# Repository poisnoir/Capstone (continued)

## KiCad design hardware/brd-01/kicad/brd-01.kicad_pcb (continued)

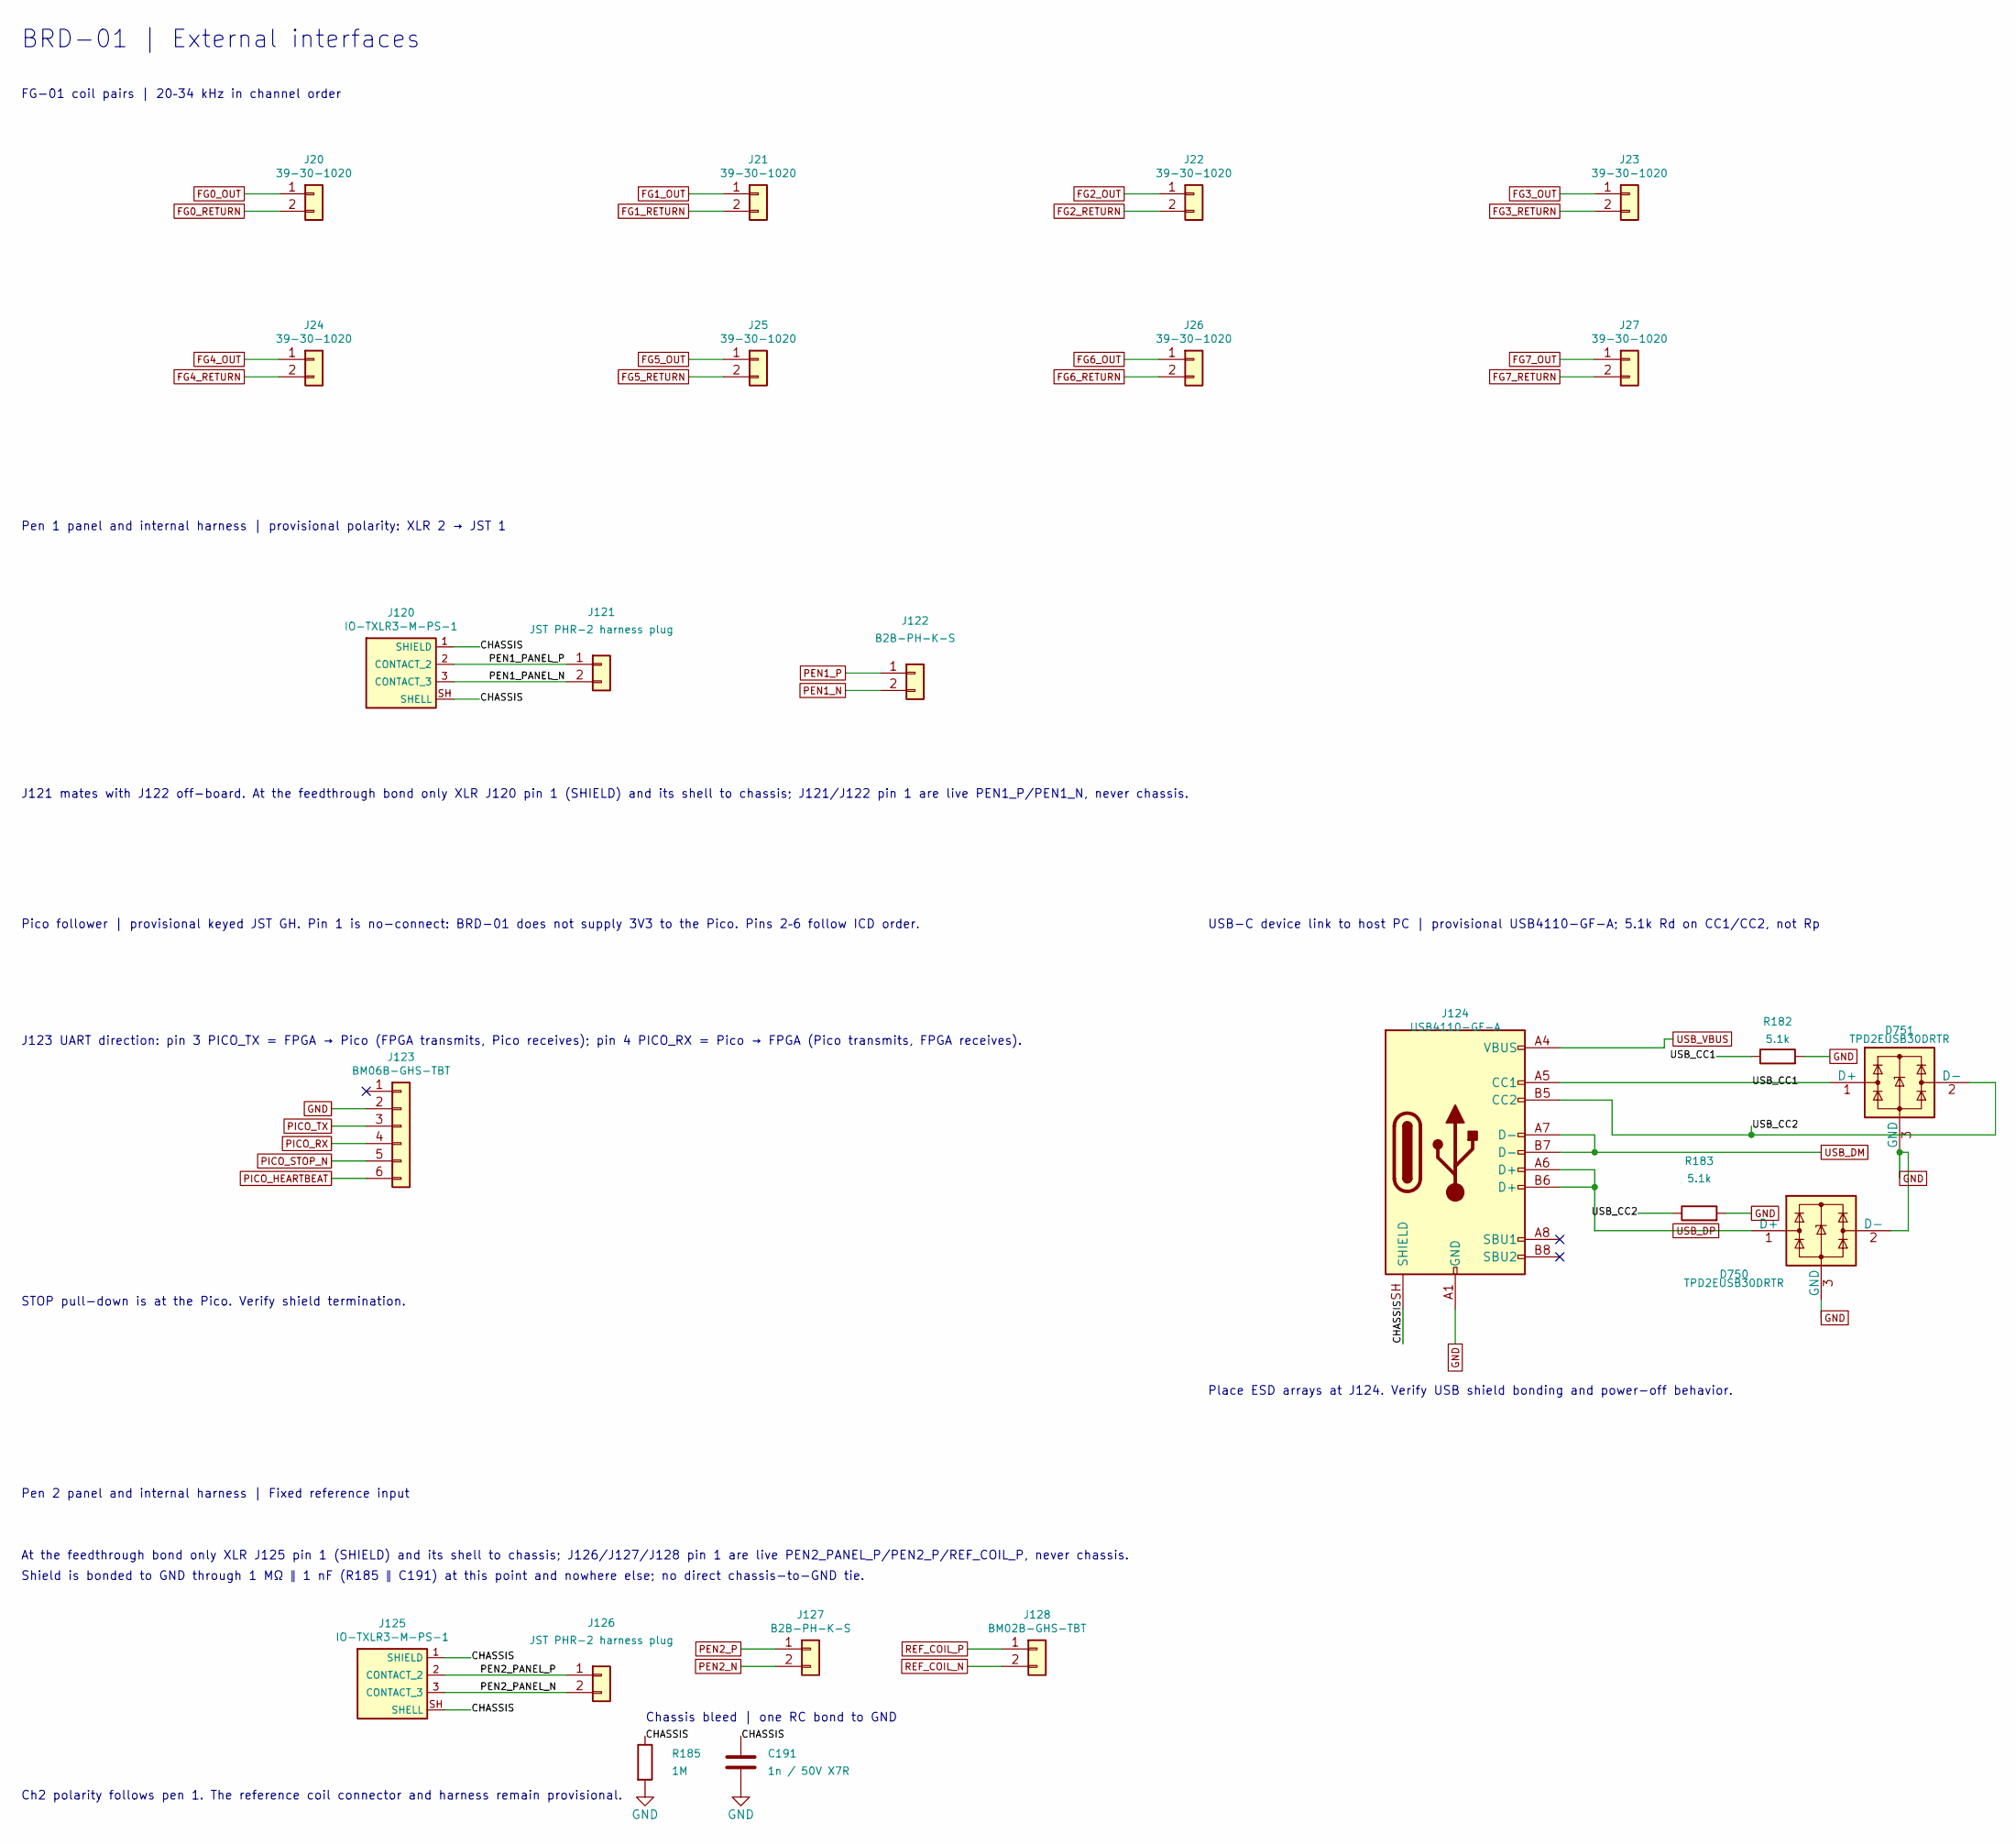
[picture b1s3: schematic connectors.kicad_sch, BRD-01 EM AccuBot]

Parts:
C191: 1n / 50V X7R; C_0603_1608Metric
D750, D751: TPD2EUSB30DRTR; Texas_DRT-3
J20, J21, J22, J23, J24, J25, J26, J27: 39-30-1020; Molex_Mini-Fit_Jr_5569-02A2_2x01_P4.20mm_Horizontal
J120, J125: IO-TXLR3-M-PS-1
J121, J126: JST PHR-2 harness plug
J122, J127: B2B-PH-K-S; JST_PH_B2B-PH-K_1x02_P2.00mm_Vertical
J123: BM06B-GHS-TBT; JST_GH_BM06B-GHS-TBT_1x06-1MP_P1.25mm_Vertical
J124: USB4110-GF-A; USB_C_Receptacle_GCT_USB4110
J128: BM02B-GHS-TBT; JST_GH_BM02B-GHS-TBT_1x02-1MP_P1.25mm_Vertical
R182, R183: 5.1k; R_0603_1608Metric
R185: 1M; R_0603_1608Metric

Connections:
/connectors/CHASSIS: C191.1, J120.1 (SHIELD), J120.SH (SHELL), J124.SH (SHIELD), J125.1 (SHIELD), J125.SH (SHELL), R185.1
/connectors/USB_CC1: D751.1 (D+), J124.A5 (CC1), R182.1
/connectors/USB_CC2: D751.2 (D-), J124.B5 (CC2), R183.1
FG0_OUT: J20.1; also elsewhere on the board
FG0_RETURN: J20.2; also elsewhere on the board
FG1_OUT: J21.1; also elsewhere on the board
FG1_RETURN: J21.2; also elsewhere on the board
FG2_OUT: J22.1; also elsewhere on the board
FG2_RETURN: J22.2; also elsewhere on the board
FG3_OUT: J23.1; also elsewhere on the board
FG3_RETURN: J23.2; also elsewhere on the board
FG4_OUT: J24.1; also elsewhere on the board
FG4_RETURN: J24.2; also elsewhere on the board
FG5_OUT: J25.1; also elsewhere on the board
FG5_RETURN: J25.2; also elsewhere on the board
FG6_OUT: J26.1; also elsewhere on the board
FG6_RETURN: J26.2; also elsewhere on the board
FG7_OUT: J27.1; also elsewhere on the board
FG7_RETURN: J27.2; also elsewhere on the board
GND: C191.2, D750.2 (D-), D750.3 (GND), D751.3 (GND), J123.2, J124.A1 (GND), J124.A12 (GND), J124.B1 (GND), J124.B12 (GND), R182.2, R183.2, R185.2; also elsewhere on the board
unnamed: J120.2 (CONTACT_2), J121.1
unnamed: J120.3 (CONTACT_3), J121.2
unnamed: J125.2 (CONTACT_2), J126.1
unnamed: J125.3 (CONTACT_3), J126.2
PEN1_N: J122.2; also elsewhere on the board
PEN1_P: J122.1; also elsewhere on the board
PEN2_N: J127.2; also elsewhere on the board
PEN2_P: J127.1; also elsewhere on the board
PICO_HEARTBEAT: J123.6; also elsewhere on the board
PICO_RX: J123.4; also elsewhere on the board
PICO_STOP_N: J123.5; also elsewhere on the board
PICO_TX: J123.3; also elsewhere on the board
REF_COIL_N: J128.2; also elsewhere on the board
REF_COIL_P: J128.1; also elsewhere on the board
USB_DM: J124.A7 (D-), J124.B7 (D-); also elsewhere on the board
USB_DP: D750.1 (D+), J124.A6 (D+), J124.B6 (D+); also elsewhere on the board
USB_VBUS: J124.A4 (VBUS), J124.A9 (VBUS), J124.B4 (VBUS), J124.B9 (VBUS); also elsewhere on the board

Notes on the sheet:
J123 UART direction: pin 3 PICO_TX = FPGA → Pico (FPGA transmits, Pico receives); pin 4 PICO_RX = Pico → FPGA (Pico transmits, FPGA receives).
Pico follower | provisional keyed JST GH. Pin 1 is no-connect: BRD-01 does not supply 3V3 to the Pico. Pins 2–6 follow ICD order.
J121 mates with J122 off-board. At the feedthrough bond only XLR J120 pin 1 (SHIELD) and its shell to chassis; J121/J122 pin 1 are live PEN1_P/PEN1_N, never chassis.
FG-01 coil pairs | 20–34 kHz in channel order
Shield is bonded to GND through 1 MΩ ∥ 1 nF (R185 ∥ C191) at this point and nowhere else; no direct chassis-to-GND tie.
USB-C device link to host PC | provisional USB4110-GF-A; 5.1k Rd on CC1/CC2, not Rp
Pen 2 panel and internal harness | Fixed reference input
Pen 1 panel and internal harness | provisional polarity: XLR 2 → JST 1
At the feedthrough bond only XLR J125 pin 1 (SHIELD) and its shell to chassis; J126/J127/J128 pin 1 are live PEN2_PANEL_P/PEN2_P/REF_COIL_P, never chassis.
BRD-01 | External interfaces
Chassis bleed | one RC bond to GND
Ch2 polarity follows pen 1. The reference coil connector and harness remain provisional.
STOP pull-down is at the Pico. Verify shield termination.
Place ESD arrays at J124. Verify USB shield bonding and power-off behavior.

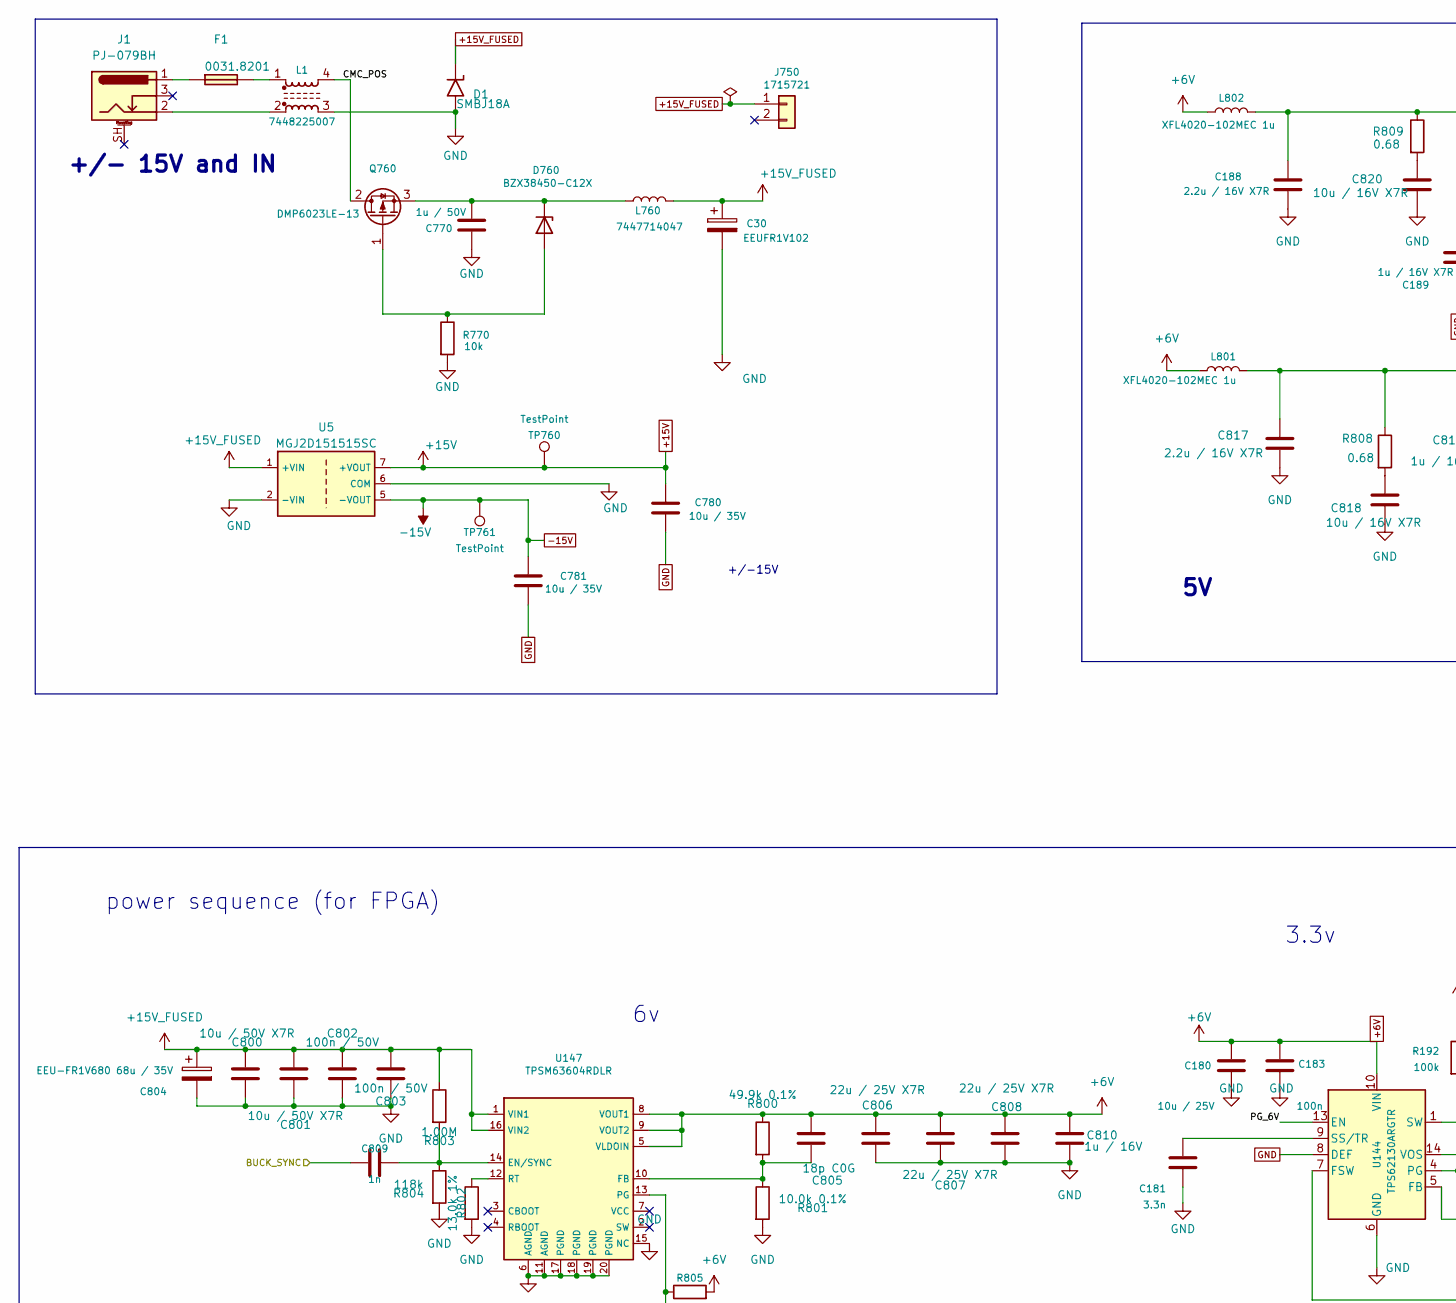
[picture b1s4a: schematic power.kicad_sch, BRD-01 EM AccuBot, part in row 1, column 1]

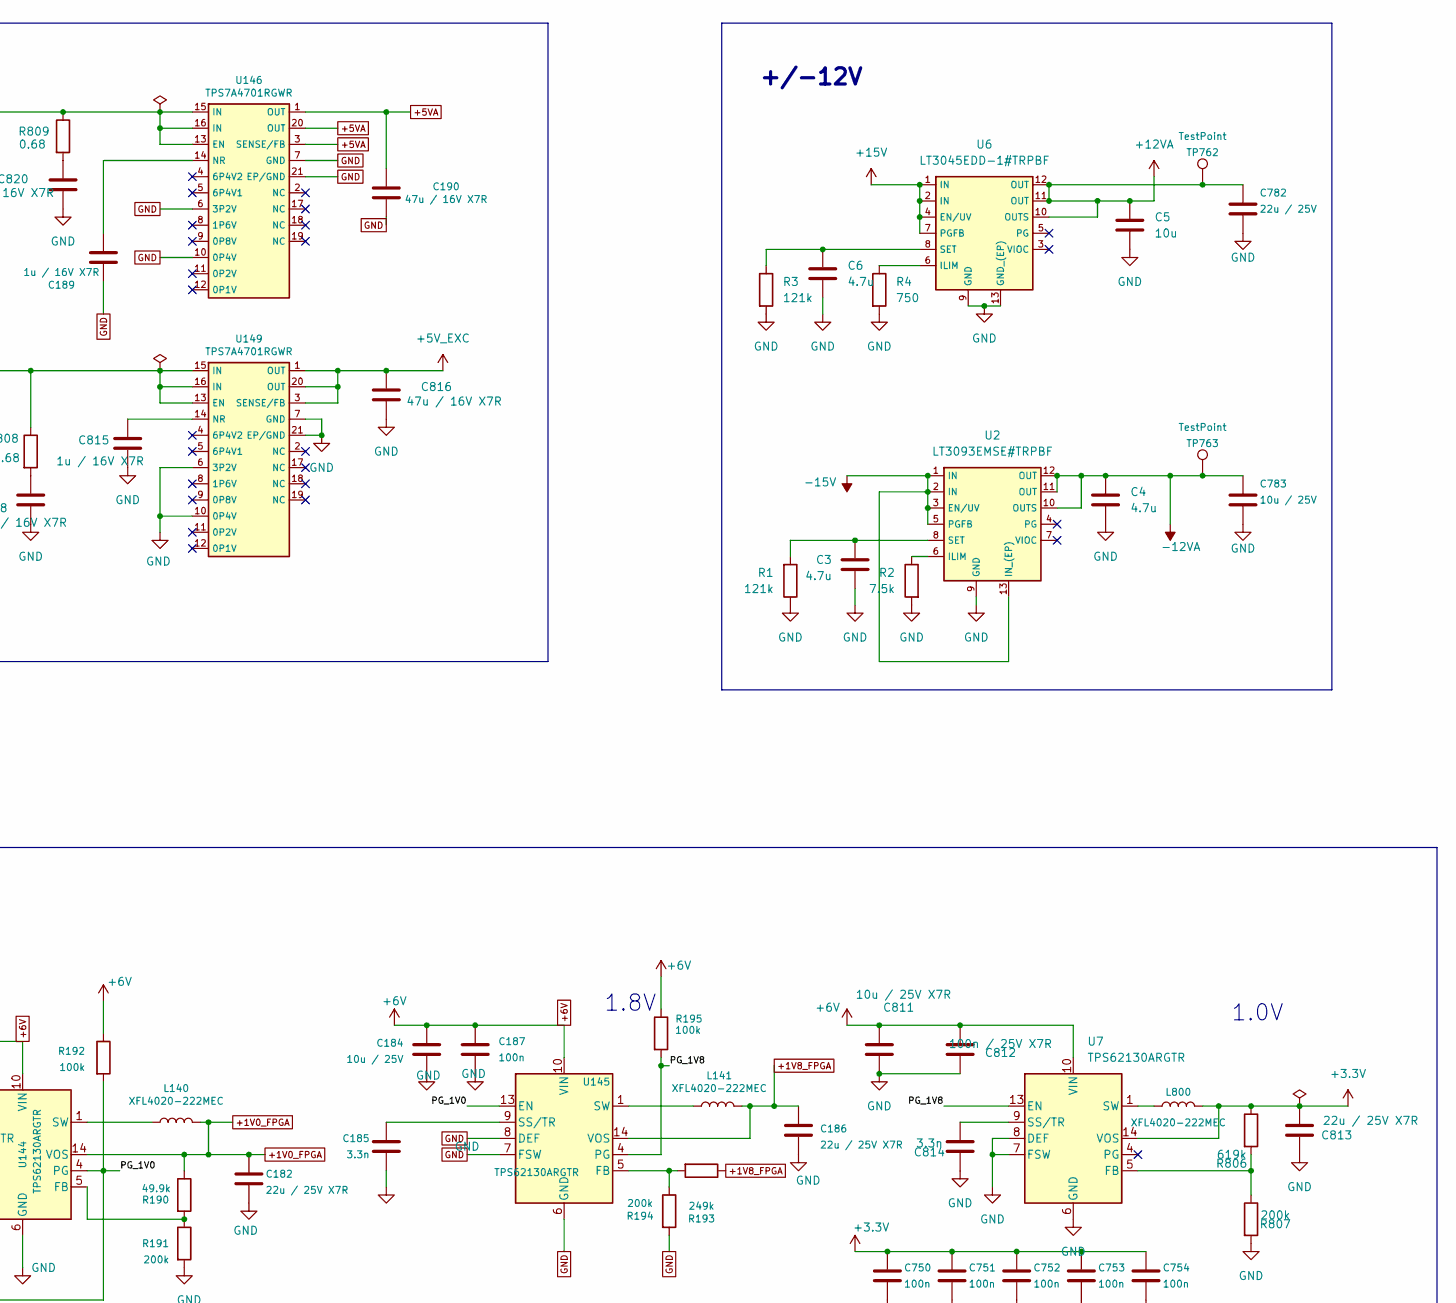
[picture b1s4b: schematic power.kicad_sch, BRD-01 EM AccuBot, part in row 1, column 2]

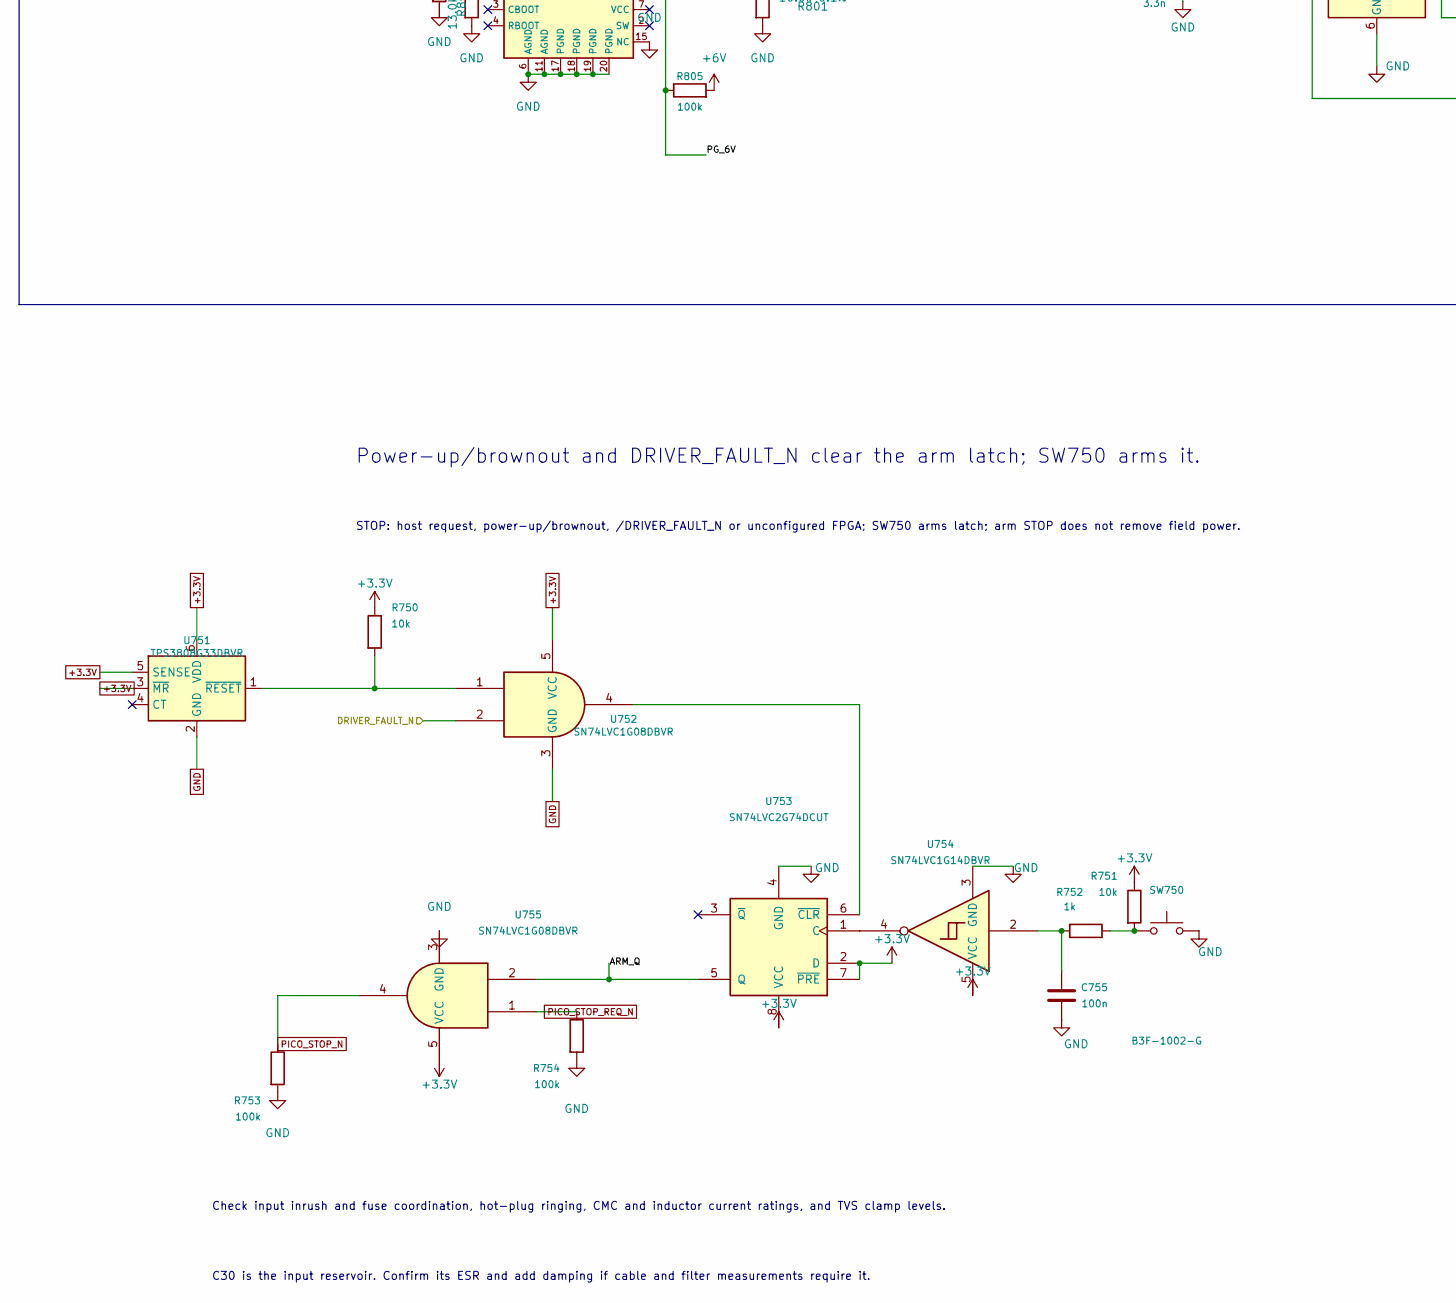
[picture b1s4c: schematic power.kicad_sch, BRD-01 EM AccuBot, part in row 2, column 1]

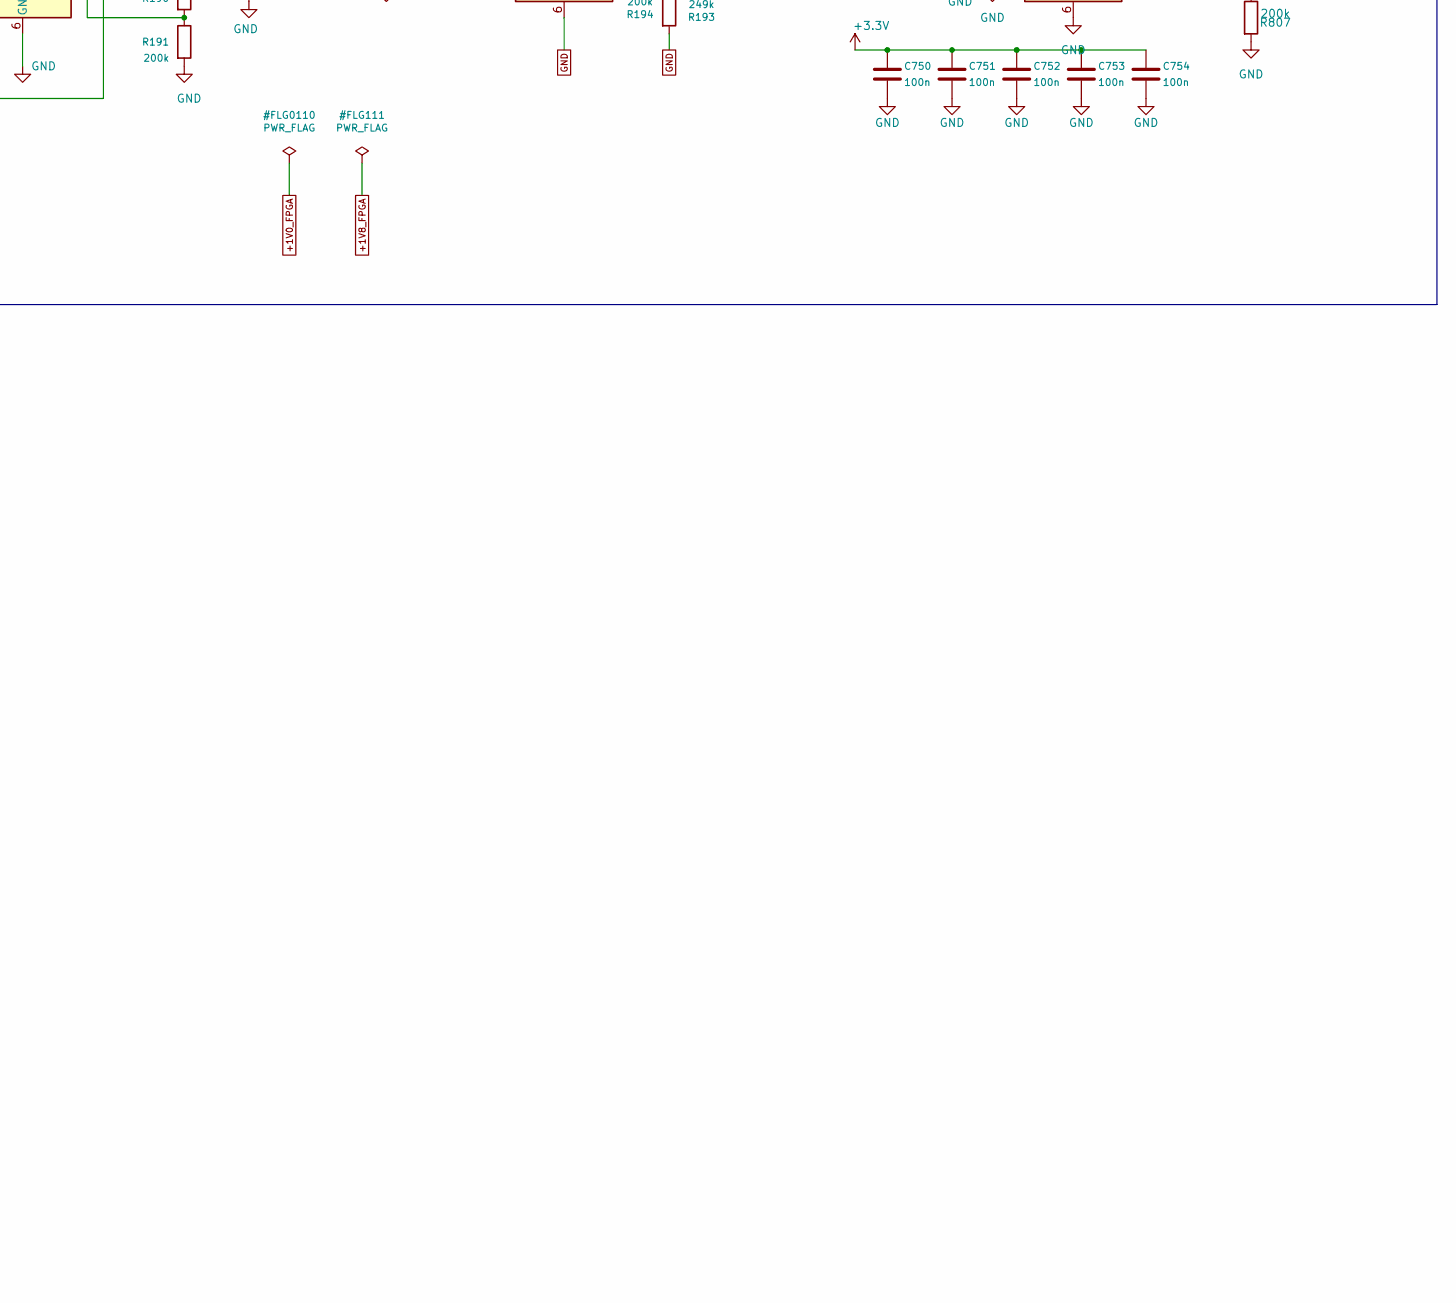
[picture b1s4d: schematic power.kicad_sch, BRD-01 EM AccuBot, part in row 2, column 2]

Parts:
C3, C6: 4.7u; C_0805_2012Metric
C4: 4.7u; C_1206_3216Metric
C5: 10u; C_1206_3216Metric
C30: EEUFR1V102; CP_Radial_D12.5mm_P5.00mm
C180, C184: 10u / 25V; C_1206_3216Metric
C181, C185, C814: 3.3n; C_0603_1608Metric
C182, C186, C806, C807, C808, C813: 22u / 25V X7R; C_1210_3225Metric
C183, C187, C750, C751, C752, C753, C754, C755: 100n; C_0603_1608Metric
C188, C817: 2.2u / 16V X7R; C_0805_2012Metric
C189: 1u / 16V X7R; C_1206_3216Metric
C190, C816: 47u / 16V X7R; C_1210_3225Metric
C770: 1u / 50V; C_1206_3216Metric
C780, C781: 10u / 35V; C_1206_3216Metric
C782: 22u / 25V; C_1210_3225Metric
C783: 10u / 25V; C_1210_3225Metric
C800, C801: 10u / 50V X7R; C_1210_3225Metric
C802, C803: 100n / 50V; C_0603_1608Metric
C804: EEU-FR1V680 68u / 35V; CP_Radial_D6.3mm_P2.50mm
C805: 18p C0G; C_0603_1608Metric
C809: 1n; C_0603_1608Metric
C810: 1u / 16V; C_0603_1608Metric
C811: 10u / 25V X7R; C_1206_3216Metric
C812: 100n / 25V X7R; C_0603_1608Metric
C815: 1u / 16V X7R; C_0603_1608Metric
C818, C820: 10u / 16V X7R; C_0805_2012Metric
D1: SMBJ18A; ST_SMBJ_DO-214AA_DS1283
D760: BZX38450-C12X; D_SOD-323
F1: 0031.8201; Fuseholder_Cylinder-5x20mm_Schurter_0031_8201_Horizontal_Op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; MPN 0001.2509
J1: PJ-079BH; BarrelJack_CUI_PJ-079BH_Horizontal
J750: 1715721; TerminalBlock_Phoenix_MKDS-1,5-2-5.08_1x02_P5.08mm_Horizont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
L1: 7448225007; Wuerth_WE-CMB-HC_S_7448225007
L140, L141, L800: XFL4020-222MEC; L_Coilcraft_XxL4020
L760: 7447714047; Wuerth_WE-PD_1050_7447714047
L801, L802: XFL4020-102MEC 1u; L_Coilcraft_XxL4020
Q760: DMP6023LE-13; SOT-223-3_TabPin2
R1, R3: 121k; R_0603_1608Metric
R2: 7.5k; R_0603_1608Metric
R4: 750; R_0603_1608Metric
R190: 49.9k; R_0603_1608Metric
R191, R194, R807: 200k; R_0603_1608Metric
R192, R195, R753, R754, R805: 100k; R_0603_1608Metric
R193: 249k; R_0603_1608Metric
R750, R751, R770: 10k; R_0603_1608Metric
R752: 1k; R_0603_1608Metric
R800: 49.9k 0.1%; R_0603_1608Metric
R801: 10.0k 0.1%; R_0603_1608Metric
R802: 13.0k 1%; R_0603_1608Metric
R803: 1.00M; R_0603_1608Metric
R804: 118k; R_0603_1608Metric
R806: 619k; R_0603_1608Metric
R808, R809: 0.68; R_0603_1608Metric
SW750: B3F-1002-G; SW_PUSH_6mm_H4.3mm
TP760, TP761, TP762, TP763: TestPoint; TestPoint_Pad_D1.5mm
U2: LT3093EMSE#TRPBF; MSOP-12-1EP_3x4.039mm_P0.65mm_EP1.651x2.845mm
U5: MGJ2D151515SC; Converter_DCDC_Murata_MGJ2DxxxxxxSC_THT
U6: LT3045EDD-1#TRPBF; DFN-12-1EP_3x3mm_P0.45mm_EP1.65x2.38mm
U7, U144, U145: TPS62130ARGTR; VQFN-16-1EP_3x3mm_P0.5mm_EP1.68x1.68mm_ThermalVias
U146, U149: TPS7A4701RGWR; Texas_RGW0020A_VQFN-20-1EP_5x5mm_P0.65mm_EP3.15x3.15mm_Ther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
U147: TPSM63604RDLR; TI_RDL0020A_B3QFN-20_5x5.5mm
U751: TPS3808G33DBVR; SOT-23-6
U752, U755: SN74LVC1G08DBVR; SOT-23-5
U753: SN74LVC2G74DCUT; VSSOP-8_2.3x2mm_P0.5mm
U754: SN74LVC1G14DBVR; SOT-23-5

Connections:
+1V0_FPGA: C182.1, L140.2, R190.1, U144.14 (VOS); also elsewhere on the board
+1V8_FPGA: C186.1, L141.2, R193.1, U145.14 (VOS); also elsewhere on the board
+3.3V: C750.1, C751.1, C752.1, C753.1, C754.1, C813.1, L800.2, R750.1, R751.1, R806.1, U7.14 (VOS), U751.3 (~MR), U751.5 (SENSE), U751.6 (VDD), U752.5 (VCC), U753.2 (D), U753.7 (~PRE), U753.8 (VCC), U754.5 (VCC), U755.5 (VCC); also elsewhere on the board
+5VA: C190.1, U146.1 (OUT), U146.3 (SENSE/FB), U146.20 (OUT); also elsewhere on the board
+5V_EXC: C816.1, U149.1 (OUT), U149.3 (SENSE/FB), U149.20 (OUT); also elsewhere on the board
+6V: C180.1, C183.1, C184.1, C187.1, C805.1, C806.1, C807.1, C808.1, C810.1, C811.1, C812.1, L801.1, L802.1, R192.1, R195.1, R800.1, R805.2, U7.10 (VIN), U7.11 (VIN), U7.12 (VIN), U144.10 (VIN), U144.11 (VIN), U144.12 (VIN), U145.10 (VIN), U145.11 (VIN), U145.12 (VIN), U147.5 (VLDOIN), U147.8 (VOUT1), U147.9 (VOUT2)
+12VA: C5.1, C782.1, TP762.1 (1_1), U6.10 (OUTS), U6.11 (OUT), U6.12 (OUT); also elsewhere on the board
+15V: C780.1, TP760.1 (1_1), U5.7 (+VOUT), U6.1 (IN), U6.2 (IN), U6.4 (EN/UV), U6.7 (PGFB)
+15V_FUSED: C30.1, C800.1, C801.1, C802.1, C803.1, C804.1, D1.1 (K), J750.1 (Pin_1_1), L760.2, R803.1, U5.1 (+VIN), U147.1 (VIN1), U147.16 (VIN2); also elsewhere on the board
-12VA: C4.1, C783.1, TP763.1 (1_1), U2.10 (OUTS), U2.11 (OUT), U2.12 (OUT); also elsewhere on the board
-15V: C781.1, TP761.1 (1_1), U2.1 (IN), U2.2 (IN), U2.3 (EN/UV), U2.5 (PGFB), U2.13 (IN_(EP)), U5.5 (-VOUT)
/BUCK_SYNC: C809.1; also elsewhere on the board
/DRIVER_FAULT_N: U752.2; also elsewhere on the board
/power/ARM_Q: U753.5 (Q), U755.2
/power/CMC_POS: L1.4, Q760.2 (D)
/power/PG_1V0: R192.2, U144.4 (PG), U144.7 (FSW), U145.13 (EN)
/power/PG_1V8: R195.2, U7.13 (EN), U145.4 (PG)
/power/PG_6V: R805.1, U144.13 (EN), U147.13 (PG)
GND: C3.2, C4.2, C5.2, C6.2, C30.2, C180.2, C181.2, C182.2, C183.2, C184.2, C185.2, C186.2, C187.2, C188.2, C189.2, C190.2, C750.2, C751.2, C752.2, C753.2, C754.2, C755.2, C770.2, C780.2, C781.2, C782.2, C783.2, C800.2, C801.2, C802.2, C803.2, C804.2, C806.2, C807.2, C808.2, C810.2, C811.2, C812.2, C813.2, C814.2, C815.2, C816.2, C817.2, C818.2, C820.2, D1.2 (A), L1.3, R1.1, R2.2, R3.2, R4.2, R191.2, R194.2, R753.2, R754.2, R770.2, R801.2, R802.2, R804.2, R807.2, SW750.2, U2.9 (GND), U5.2 (-VIN), U5.6 (COM), U6.9 (GND), U6.13 (GND_(EP)), U7.6 (GND), U7.7 (FSW), U7.8 (DEF), U7.15 (GND), U7.16 (GND), U7.17 (GND), U144.6 (GND), U144.8 (DEF), U144.15 (GND), U144.16 (GND), U144.17 (GND), U145.6 (GND), U145.7 (FSW), U145.8 (DEF), U145.15 (GND), U145.16 (GND), U145.17 (GND), U146.6 (3P2V), U146.7 (GND), U146.10 (0P4V), U146.21 (EP/GND), U147.6 (AGND), U147.11 (AGND), U147.15 (NC), U147.17 (PGND), U147.18 (PGND), U147.19 (PGND), U147.20 (PGND), U149.6 (3P2V), U149.7 (GND), U149.10 (0P4V), U149.21 (EP/GND), U751.2 (GND), U752.3 (GND), U753.4 (GND), U754.3 (GND), U755.3 (GND); also elsewhere on the board
unnamed: C755.1, R752.2, U754.2
unnamed: C818.1, R808.2
unnamed: C820.1, R809.2
unnamed: D760.2 (A), Q760.1 (G), R770.1
unnamed: C770.1, D760.1 (K), L760.1, Q760.3 (S)
unnamed: F1.1, J1.1
unnamed: F1.2, L1.1
unnamed: J1.2, L1.2
unnamed: L140.1, U144.1 (SW), U144.2 (SW), U144.3 (SW)
unnamed: L141.1, U145.1 (SW), U145.2 (SW), U145.3 (SW)
unnamed: L800.1, U7.1 (SW), U7.2 (SW), U7.3 (SW)
unnamed: R751.2, R752.1, SW750.1
unnamed: R2.1, U2.6 (ILIM)
unnamed: C3.1, R1.2, U2.8 (SET)
unnamed: R4.1, U6.6 (ILIM)
unnamed: C6.1, R3.1, U6.8 (SET)
unnamed: R806.2, R807.1, U7.5 (FB)
unnamed: C814.1, U7.9 (SS/TR)
unnamed: R190.2, R191.1, U144.5 (FB)
unnamed: C181.1, U144.9 (SS/TR)
unnamed: R193.2, R194.1, U145.5 (FB)
unnamed: C185.1, U145.9 (SS/TR)
unnamed: C188.1, L802.2, R809.1, U146.13 (EN), U146.15 (IN), U146.16 (IN)
unnamed: C189.1, U146.14 (NR)
unnamed: C809.2, R803.2, R804.1, U147.14 (EN/SYNC)
unnamed: C805.2, R800.2, R801.1, U147.10 (FB)
unnamed: R802.1, U147.12 (RT)
unnamed: C817.1, L801.2, R808.1, U149.13 (EN), U149.15 (IN), U149.16 (IN)
unnamed: C815.1, U149.14 (NR)
unnamed: R750.2, U751.1 (~RESET), U752.1
unnamed: U753.1 (C), U754.4
unnamed: U752.4, U753.6 (~CLR)
PICO_STOP_N: R753.1, U755.4; also elsewhere on the board
PICO_STOP_REQ_N: R754.1, U755.1; also elsewhere on the board

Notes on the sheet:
Power-up/brownout and DRIVER_FAULT_N clear the arm latch; SW750 arms it.
+/-12V
+/- 15V and IN
C30 is the input reservoir. Confirm its ESR and add damping if cable and filter measurements require it.
3.3v
Check input inrush and fuse coordination, hot-plug ringing, CMC and inductor current ratings, and TVS clamp levels.
1.0V
1.8V
STOP: host request, power-up/brownout, /DRIVER_FAULT_N or unconfigured FPGA; SW750 arms latch; arm STOP does not remove field power.
power sequence (for FPGA)
+/-15V
